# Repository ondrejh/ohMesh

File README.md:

# ohMesh

Tady si schovávám svoje pokusy se sítí Meshtastic. Začal sem s tím někdy začátkem zimy 2024. Zatím mám 1 statickou (ohM1) a jednu mobilní (ohM2) stanici na bázi modulu Heltec V3. Pak jsem postavil ještě jednu tu mobilní pro svého kamaráda. Ta je prakticky shodná s tou mojí.
Na další pokusy mám připravený další modul Heltec V3 (byl v akci) a na breadboardu stanici s Raspberry Pi Pico (ohM3).

# ohM1

Statická stanice na bázi Heltec V3. Navíc má snímač prostředí BME280 a napájecí obvod aby mohla být připojená na 12V.

Zařízení je v provozu od prosince 2024. Mělo to být dočasné řešení, něco jako pokus, ale zatím jsem s tím spokojený.

# ohM2

Mobilní vysílačka na bázi Heltec V3. Navíc má GPS modul, aby mohla reportovat polohu.

Víc podrobností v [adresáři ohm2](https://github.com/ondrejh/ohMesh/tree/master/ohm2#readme)

# ohM3

První stanice s RP2040. Zatím je ve stádiu BreadTastic Pico.

Víc podrobností v [adresáři ohm3](https://github.com/ondrejh/ohMesh/tree/master/ohm3#readme)

# ohM4

Node na bázi Seeed Xiao NRF52840 Kit. S ambicí nahradit žravý ohM2.

Víc podrobností v [adresáři ohm4](https://github.com/ondrejh/ohMesh/tree/master/ohm4#readme)

## Linky (Zatím netříděné)

[Anténa ohM1 (Aliexpress)](https://www.aliexpress.com/item/1005006833587735.html?spm=a2g0o.order_list.order_list_main.131.3e601802HxDH7p)

[Měření tlaku, vlhkosti a teploty, BME280 (Aliexpress)](https://www.aliexpress.com/item/1005004527984343.html?spm=a2g0o.order_list.order_list_main.106.3e601802HxDH7p)

[Samostatný LoRa module SX1262 (Aliexpress)](https://www.aliexpress.com/item/1005005868418525.html?spm=a2g0o.order_list.order_list_main.59.3e601802HxDH7p)

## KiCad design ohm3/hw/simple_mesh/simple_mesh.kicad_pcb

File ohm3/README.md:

# Stanice s Raspberry PI pico ohM3

Dalším mým pokusem s Meshtastikem je stanice postavená na základě [Raspberry PI Pico s kontrolérem RP2040](https://www.raspberrypi.com/documentation/microcontrollers/pico-series.html#pico-1-family). LoRa konektivitu zde zajišťuje [modul SX1262](https://www.aliexpress.com/item/1005005868418525.html?spm=a2g0o.order_list.order_list_main.59.3e601802HxDH7p). Stanice je zatím postavená na nepájivé desce, breadboardu, takže jsem jí dal pracovní název BreadTastic Pico (ne, není to Ostravsky, bez diakritiky).

Toto zapojení funguje s firmwarem varianty [rpipico](https://github.com/meshtastic/firmware/tree/master/variants/rpipico).

Stanici jsem později doplnil o čidlo prostředí, aby to ukazovalo nějaká pěkná čísla. Dál taky o displej, baterku ... Teď mám v plánu GPS, aby to bylo kompletní.

## Základní zapojení

Úplně minimální stanice s Raspberry PI Pico potřebuje ke své funkci, kromě samotného [Raspberry](https://www.raspberrypi.com/documentation/microcontrollers/pico-series.html#pico-1-family), už jen LoRa modul [SX1262](https://www.aliexpress.com/item/1005005868418525.html?spm=a2g0o.order_list.order_list_main.59.3e601802HxDH7p) a [anténu](https://www.aliexpress.com/item/32957518009.html?spm=a2g0o.order_list.order_list_main.75.19f61802j9j96w).

Pico | SX1262
--- | ---
GND | GND
3V3(OUT) | 3V3
GP2 | BUSY
GP3 | CS
GP10 | CLK
GP11 | MOSI
GP12 | MISO
GP15 | RESET
GP20 | DIO1

Zapojení vychází z [modulu SX1262 LoRa Node od WaveShare](https://www.waveshare.com/pico-lora-sx1262-868m.htm).

Pozn.:
1) Všiml jsem si, že zapojení úplně nesedí se souborem varian.h. Tam je GP2 připojené na DIO2, místo na BUSY. Nicméně to funguje. Na dalším řádku se totiž uvádí ```#define SX126X_BUSY LORA_DIO2```, takže asi proto.
2) Na breadboardu se mi odpojil GP15 - RESET, a zařízení vesele funguje dál. Kdyby bylo třeba šetřit GPIO, šlo by to asi nastavit unset.

### Nastavení pomocí meshtastic python cli

Nastavení regionu a presetu:
``` code
meshtastic --port /dev/ttyACM0 \
  --set lora.region EU_868 \
  --set lora.modem_preset MEDIUM_FAST \
  --reboot
```

Nastavení jména nodu:
``` code
meshtastic --port /dev/ttyACM0 \
  --set device.node_info.long_name "My New Node" \
  --set device.node_info.short_name "MNND" \
  --reboot
```

Nastavení defaultního primárního kanálu:
``` code
meshtastic --port /dev/ttyACM0 \
  --ch-index 0
  --ch-set name MediumFast
  --ch-set psk default
```

## Připojení čidla prostředí BME280

K původnímu zapojení jsem se nejdřív pokoušel hledat správné piny pro připojení snímačů prostředí. Vybral jsem si čidlo [BME280](https://www.aliexpress.com/item/1005004527984343.html?spm=a2g0o.order_list.order_list_main.127.19f61802j9j96w), které už mám připojené ke statické stanici ohM1. Při nákupu čidla je třeba vybrat variantu BME280 na 3V3. Prodejci často nabízejí take BMP280, které je mnohem levnější, ale neměří vlhkost. S Meshtastikem nicméně funguje také.

Zdá se, že v oficiálním FW pro Meshtastic na Raspberry PI Pico není I2C pro telemetrii podporováno. Nebo prostě nevím jak. Rozhodl jsem se tedy přistoupit úpravě FW.

Připojil jsem snímač na piny 6 a 7, kam je možné namapovat I2C1. Tyto piny jsem exlicitně uvedl ve variantě pro překlad a firmware si zkompiloval sám. Postup kompilace je uvedený na webu [meshtastic.org](https://meshtastic.org/docs/development/firmware/build/), takže uvedu jen body.

Pozn.: Výběr čidla BME280 možná nebyl ten nejšťastnější. Vybral jsem ho hlavně proto, že jsem ho měl v šuplíku, a také proto, že mám stejné čidlo připojené k statické stanici ohM1. Zdá se ale, že specificky BME280, nefunguje s Raspberry PI. Uvádí se to zde: [github meshtastic firmware issue 5361](https://github.com/meshtastic/firmware/issues/5361). Chyba je opravená ve verzi FW 2.6.+, která v době, kdy jsem to zkoušel, byla ještě alfa. Každopádně, vlastním buildem FW, se toto vyřešilo.

### Zapojení snímače

Pico | BME280
--- | ---
GND | GND
3V3(OUT) | 3V3
GP6 | SDA
GP7 | SCL

### Úprava FW aby podporoval moduly I2C

- instalace Visual Studio Code s doplňkem PlatformIO
- stažení githubového repozitáře s fimwarem
- výběr cílového zařízení rpipico
- úprava souboru variant.h, přidání I2C pinů
- kompilace a upload

#### Úprava souboru variant.h

Za poznámku o defaultních I2C pinech (4/5) jsem přidal definici pinů I2C_SDA, I2C_SCL, I2C_SDA1 a I2C_SCL1. Asi by stačilo přidat jen ty s jedničkou, ale teď mám alespoň jistotu, až budu chtít třeba přidat displej.

```code
// default I2C pins:
// SDA = 4
// SCL = 5

// Redefine I2C0 pins to avoid collision with UART1/Serial2.
#define I2C_SDA 4
#define I2C_SCL 5

// Redefine Waveshare UPS-A/B I2C_1 pins:
#define I2C_SDA1 6
#define I2C_SCL1 7

// Recommended pins for SerialModule:
// txd = 8
// rxd = 9
```

#### Upload firmwaru

Projek ve Visual Studiu předpokládá nahrávání FW pomocí debugovacího rozhraní, které ale nemám - ještě jsem ho nepotřeboval. Naštěstí se při překladu vytvoří i soubor firmware.u2f, který se nahrává do zařízení jako na flash disk. Tak jak je to ve všech návodech pro začátečníky.

### Zapnutí Telemetrie

Snímače na I2C nezačnou samy od sebe pracovat, je třeba je zapnout tzv. Modul Telemetrie. Ve webovém rozhraní [Meshtastic Web](https://client.meshtastic.org/) se mi to bohužel nedařilo, takže uvedu postup pro Meshtastick Python CLI.

```code
python3 -m meshtastic --set telemetry.environment_measurement_enabled true
```

Někdy je třeba uvést port, protože Python CLI nemůže stanici najít, ale tentokrát to vyšlo.

Takhle to pak vypadá, když takovou stanici vidí jiná stanice (tentokrát šlo o mou vysílačku ohM2).

## Připojení napájecího článku

Ve většině aplikací bude nejspíš podobný meshtastický uzel pracovat z baterie. Toto je ve firmwaru už podporováno, stačí tedy jen připojit článek s nabíjecím modulem a pár odporů jako dělič, pro snímání napětí baterie.

### Materiál

- článek 18650
- [nabíjecí modul](https://www.aliexpress.com/item/1005001688742632.html?spm=a2g0o.order_list.order_list_main.43.1a441802W3wg30)
- odpory 100k a 200k (nejlépe přesné)
- nějaký malý keramický kondenzátor
- dioda (nejlépe s malým úbytkem napětí)

### Zapojení

Do zapojení jsem také přidal diodu, kondenzátor a vypínač. Bez diody by se musel článek odpojovat, když se chceme připojit k USB na Raspberry PI. Kondenzátor je na potlačení šumu měření a vypínač se u článku vždycky hodí.

Napájecí článek je umístěný ve vytisknutém držáku ([model ve Freecadu](./model/breadboard_batery_holder.FCStd), [export pro slicer](./model/breadboard_batery_holder.3fm)). Do držáku se zespodu pájkou píchnou kolíky z pinové lišty a je z toho breadtastický držák.

### Funkce

Takhle to pak vypadá, když ten node vidíte ze sítě meshtastic. On tam ten stav baterie byl i předtím, ale ukazoval nesmysly, protože tam prostě ten článek chyběl. Nic se nenastavuje, prostě to chodí.

## Připojení displeje SSD1306 a tlačítka

Základní firmware také přímo podporuje připojení oled displeje SSD1306 s rozlišením 128x64 pixelů. Na displeji je možné zapnout autorotaci, nebo jednotlivé stránky rotovat tlačítkem. Tak ho taky zapojím. Pro displej sice zatím aplikaci nemám, ale zkusím to, aby to bylo kompletní.

### Zapojení

Pico | SSD1306
--- | ---
GND | GND
3V3(OUT) | 3V3
GP4 | SDA
GP5 | SCL

Pico | Tlačítko
--- | ---
GND | GND
GP18 | BTN

## Funkce

Ani pro funkci displeje není třeba nic nastavovat. Jen zapojit. Maximálně je možné nastavit zobrazení naměřených hodnot z čidel, nebo autorotaci displeje.

## Připojení GPS modulu

In progress...

První pokus jsem udělal s GPS modulem který jsem dosud používal na Heltec V3 Nody (Ohm2 a jiné). Výsledky bohužel nebyly přesvědčivé a tak jsem objednal jiný modul, menší, podobnější modulu Waveshare Pico GPS L76B který je uváděný v souboru varian.h v adresáři rpipico-slowclock. Zdá se totiž, že udělat z raspberry pi pico maximálně univerzální node se už někdo pokusil. Výsledek je tedy nejspíš tato varinta.
S tím sem už pozici přesvědčivě chytil. Ovšem, z lenosti, sem měl zapojenou větší anténu. S novým modulem se dodává malá, podlouhlá, s tou sem zatím neuspěl.

Pico | NEO-M8N
--- | ---
GP0 | TX
GP1 | RX
GP16 | PPS - nevím na co je, snad se ho půjde zbavit

Pokračování příště... Doplním jak to měří a vůbec...

# ToDo

- [x] doplnit schéma zapojení SX1262
- [x] doplnit schéma zapojení BME280
- [x] přidat baterku s nabíječkou
- [x] přidat displej
- [ ] přidat gps přijímač
- [ ] měření spotřeby

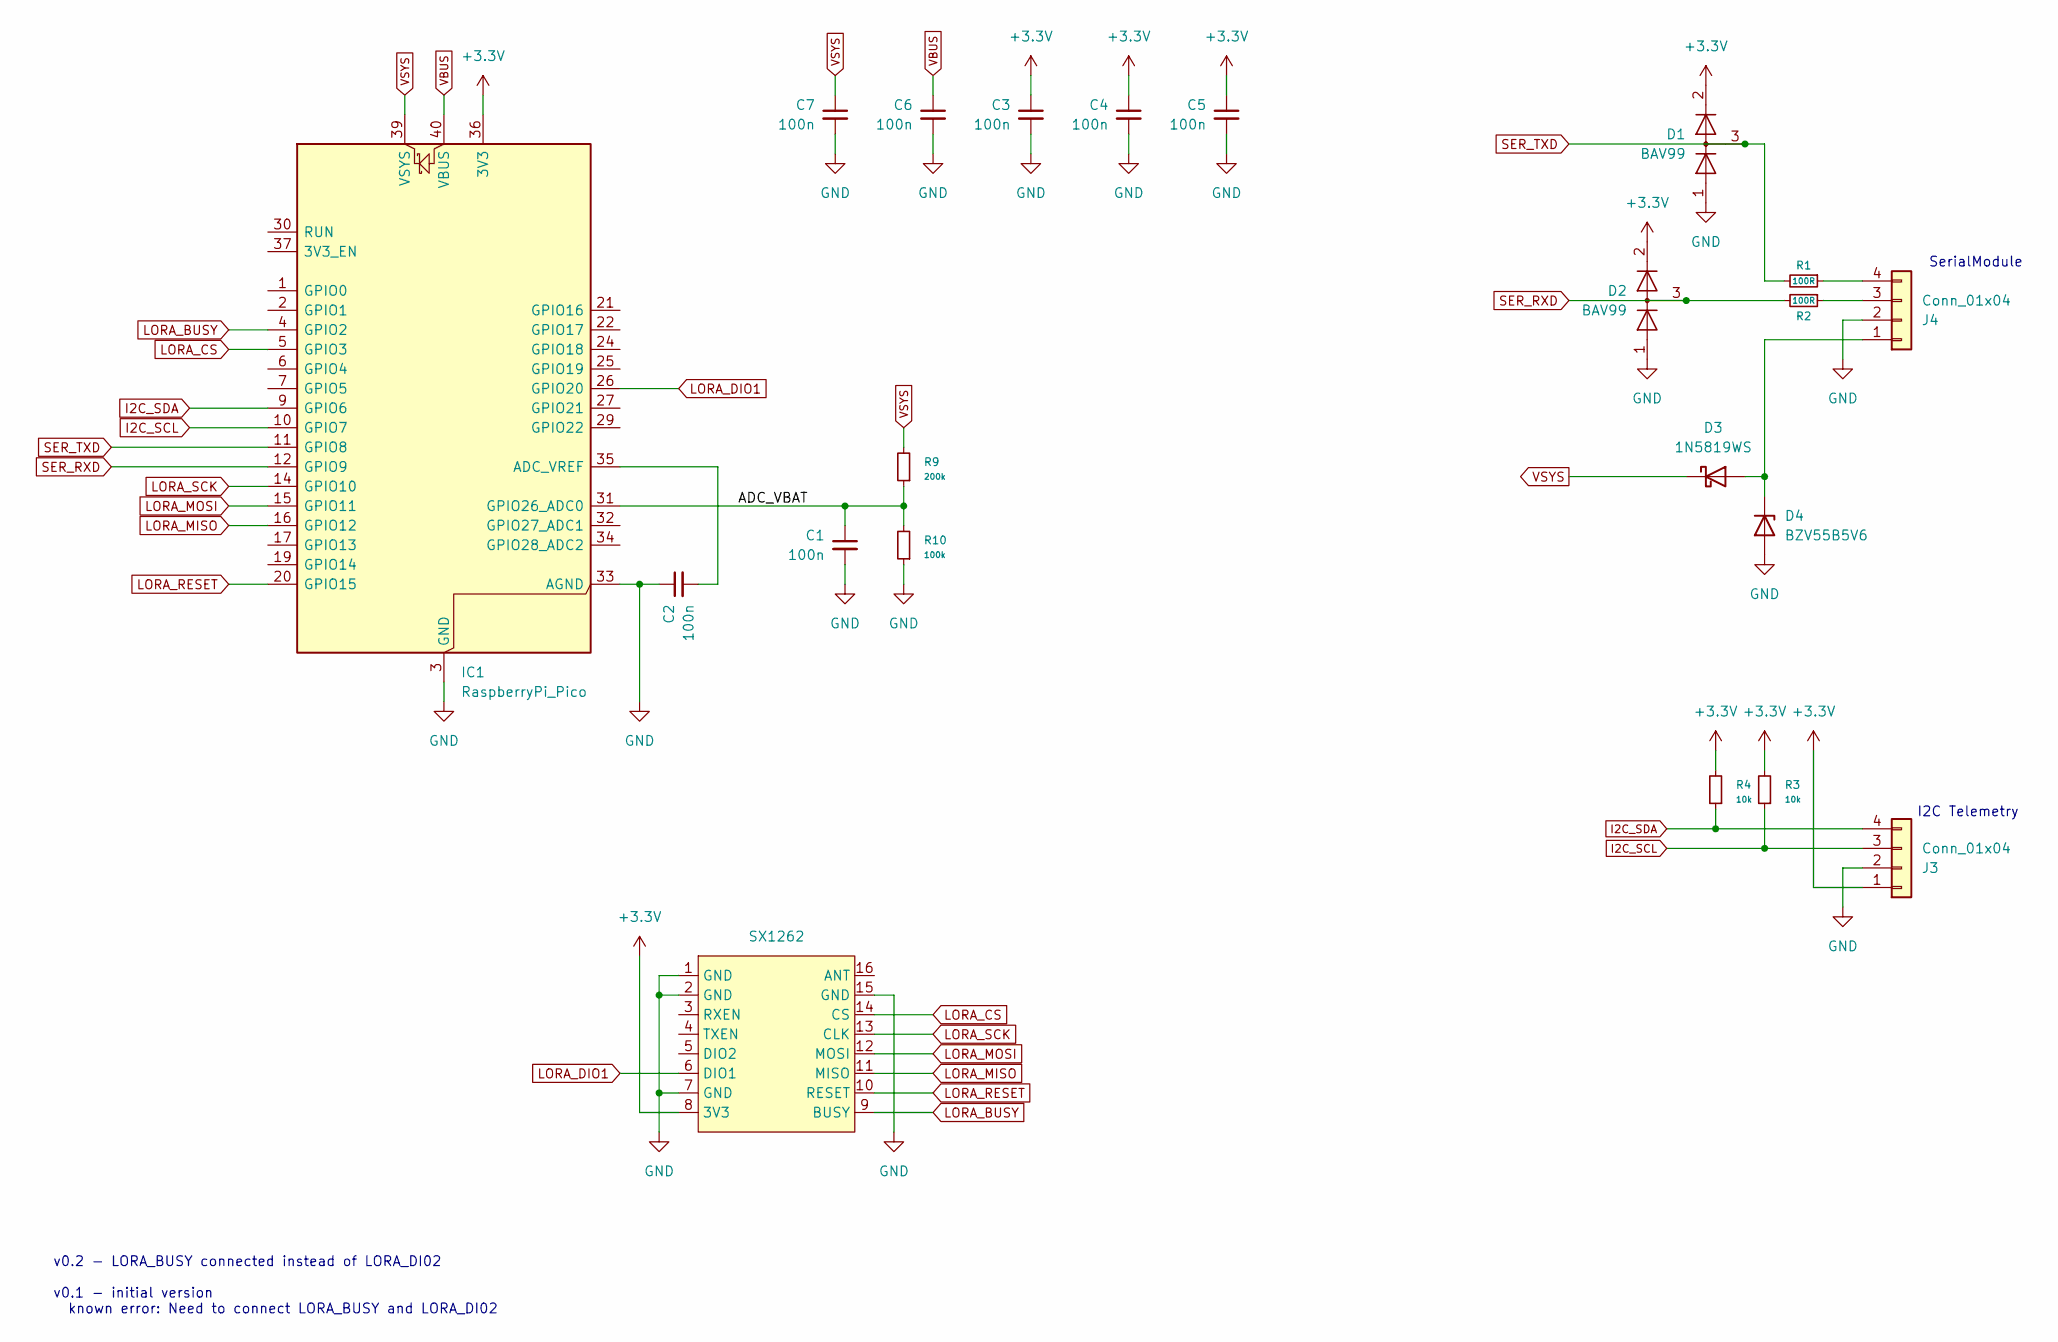
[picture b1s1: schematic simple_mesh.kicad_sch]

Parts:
C1, C2, C3, C4, C5, C6, C7: 100n; C_0603_1608Metric
D1, D2: BAV99; SOT-23
D3: 1N5819WS; D_SOD-123F
D4: BZV55B5V6; D_SMA
IC1: RaspberryPi_Pico; RaspberryPi_Pico_SMD_HandSolder
IC2: SX1262; SX1262_Core
J3, J4: Conn_01x04; solder_term_4
R1, R2: 100R; R_0603_1608Metric
R3, R4: 10k; R_0603_1608Metric
R9: 200k; R_0603_1608Metric
R10: 100k; R_0603_1608Metric

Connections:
+3.3V: C3.1, C4.1, C5.1, D1.2 (A), D2.2 (A), IC1.36 (3V3), IC2.8 (3V3), J3.1, R3.2, R4.2
/ADC_VBAT: C1.1, IC1.31 (GPIO26_ADC0), R9.1, R10.2
GND: C1.2, C2.1, C3.2, C4.2, C5.2, C6.2, C7.2, D1.1 (K), D2.1 (K), D4.2 (A), IC1.3 (GND), IC1.8 (GND), IC1.13 (GND), IC1.18 (GND), IC1.23 (GND), IC1.28 (GND), IC1.33 (AGND), IC1.38 (GND), IC2.1 (GND), IC2.2 (GND), IC2.7 (GND), IC2.15 (GND), J3.2, J4.2, R10.1
I2C_SCL: IC1.10 (GPIO7), J3.3, R3.1
I2C_SDA: IC1.9 (GPIO6), J3.4, R4.1
LORA_BUSY: IC1.4 (GPIO2), IC2.9 (BUSY)
LORA_CS: IC1.5 (GPIO3), IC2.14 (CS)
LORA_DIO1: IC1.26 (GPIO20), IC2.6 (DIO1)
LORA_MISO: IC1.16 (GPIO12), IC2.11 (MISO)
LORA_MOSI: IC1.15 (GPIO11), IC2.12 (MOSI)
LORA_RESET: IC1.20 (GPIO15), IC2.10 (RESET)
LORA_SCK: IC1.14 (GPIO10), IC2.13 (CLK)
unnamed: D3.2 (A), D4.1 (K), J4.1
unnamed: C2.2, IC1.35 (ADC_VREF)
unnamed: J4.3, R2.1
unnamed: J4.4, R1.1
SER_RXD: D2.3 (K), IC1.12 (GPIO9), R2.2
SER_TXD: D1.3 (K), IC1.11 (GPIO8), R1.2
VBUS: C6.1, IC1.40 (VBUS)
VSYS: C7.1, D3.1 (K), IC1.39 (VSYS), R9.2

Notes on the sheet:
v0.2 - LORA_BUSY connected instead of LORA_DI02 v0.1 - initial version known error: Need to connect LORA_BUSY and LORA_DI02
I2C Telemetry
SerialModule

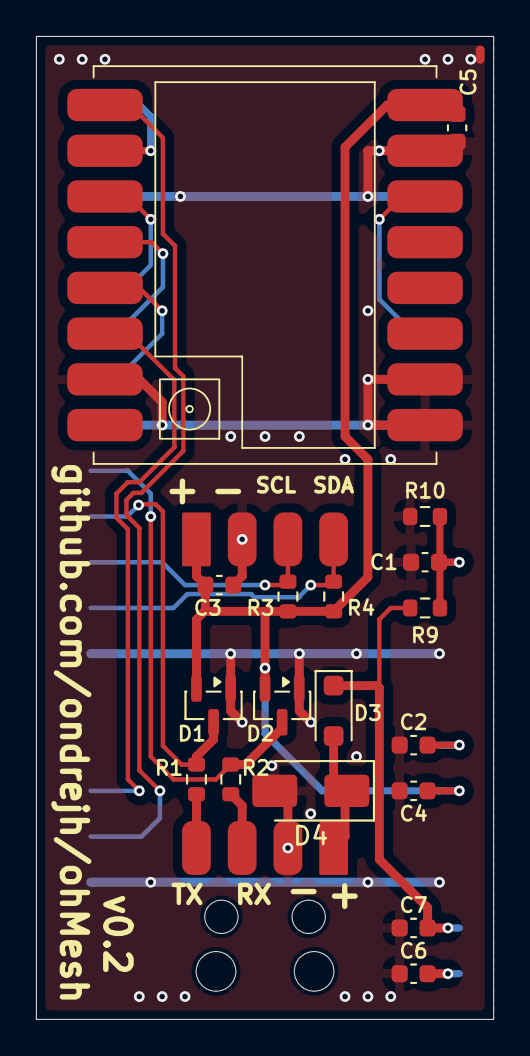
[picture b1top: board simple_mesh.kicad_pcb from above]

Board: 2 copper layers, 25.4 x 54.6 mm, 21 parts (1 on the bottom side), 20 nets.

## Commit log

2025-03-13 ladeni noveho repo
2025-03-13 ohm1 snapshot
2025-03-13 ohm2/3 title photos
2025-03-13 ohm2 folder
2025-03-13 ohm2 bom
2025-03-13 link to ohm2
2025-03-13 some links
2025-03-22 bme280 na ohm3
2025-03-23 basic station schematic
2025-03-23 connecting bme280 - schematic
2025-03-23 ohm3/img/pripojeni_bme280.odg
2025-03-23 debug: chyba zapojeni
2025-04-06 some 3d models
2025-04-06 batterymanagement
2025-04-06 ohm3 dislay ssd1306
2025-05-06 gps module and some re-wiring
2025-05-07 images, some notes
2025-05-17 heltec v3 mobile build
2025-05-17 build images (from html galery)
2025-05-18 ohm2 alternative model description
2025-05-18 typos
2025-05-18 los antenos
2025-05-18 link typo
2025-05-28 new charger - holder, for new cables
2025-05-28 more consistent image of the charger model
2025-05-29 grinding edges
2025-06-28 node backup-upgrade-restore tutorial
2025-06-28 typos a blaboly
2025-07-27 servis a update FW ohm1
2025-07-27 oprava linku
2025-11-19 prototype board supports
2025-11-19 simple mesh pcb factory
2025-11-19 pack gerber
2025-11-23 some new files
2025-11-23 heltec3 charger repair - bypass
2025-11-23 low power node
2025-12-13 html bom
2025-12-13 BUG - need to connect BUSY to DI02
2025-12-17 need 1mm more space ..
